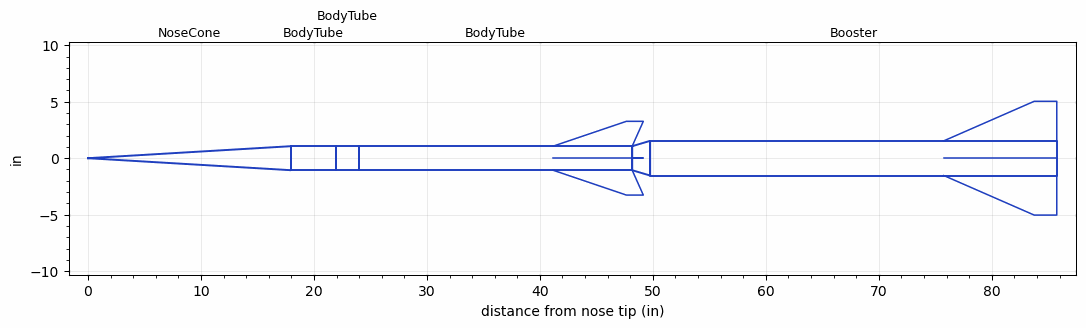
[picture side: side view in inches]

<RASAeroDocument>
 <FileVersion>2</FileVersion>
 <RocketDesign>
  <NoseCone>
   <Length>17.9685</Length>
   <Diameter>2.126</Diameter>
   <Shape>Conical</Shape>
   <Location>0</Location>
  </NoseCone>
  <BodyTube>
   <Length>4</Length>
   <Diameter>2.126</Diameter>
   <Location>17.9685</Location>
  </BodyTube>
  <BodyTube>
   <Length>2</Length>
   <Diameter>2.126</Diameter>
   <Location>21.9685</Location>
  </BodyTube>
  <BodyTube>
   <Length>24.2035</Length>
   <Diameter>2.126</Diameter>
   <Location>23.9685</Location>
   <Fin>
    <Count>4</Count>
    <Chord>7.0079</Chord>
    <Span>2.2008</Span>
    <SweepDistance>6.4921</SweepDistance>
    <TipChord>1.5</TipChord>
    <Thickness>0.1181</Thickness>
    <Location>7.0079</Location>
    <AirfoilSection>Subsonic NACA</AirfoilSection>
   </Fin>
  </BodyTube>
  <Booster>
   <Length>35.9999</Length>
   <Diameter>3.0709</Diameter>
   <InsideDiameter>2.126</InsideDiameter>
   <Location>48.172</Location>
   <ShoulderLength>1.5866</ShoulderLength>
   <Fin>
    <Count>4</Count>
    <Chord>10</Chord>
    <Span>3.5</Span>
    <SweepDistance>8</SweepDistance>
    <TipChord>2</TipChord>
    <Thickness>0.1181</Thickness>
    <Location>10</Location>
    <AirfoilSection>Subsonic NACA</AirfoilSection>
   </Fin>
  </Booster>
  <Surface>Rough Camouflage Paint</Surface>
  <ModifiedBarrowman>False</ModifiedBarrowman>
  <Turbulence>False</Turbulence>
  <UseBooster1>True</UseBooster1>
  <UseBooster2>False</UseBooster2>
 </RocketDesign>
 <LaunchSite>
  <Altitude>0</Altitude>
  <Pressure>29.9214</Pressure>
  <RodAngle>0</RodAngle>
  <RodLength>3.2808</RodLength>
  <Temperature>59</Temperature>
  <WindSpeed>4.4739</WindSpeed>
 </LaunchSite>
 <Recovery>
  <Altitude1>656.168</Altitude1>
  <Altitude2>0</Altitude2>
  <DeviceType1>Parachute</DeviceType1>
  <DeviceType2>None</DeviceType2>
  <Event1>True</Event1>
  <Event2>False</Event2>
  <Size1>47.9999</Size1>
  <Size2>0</Size2>
  <EventType1>Apogee</EventType1>
  <EventType2>None</EventType2>
  <CD1>0.8</CD1>
  <CD2>0</CD2>
 </Recovery>
 <SimulationList>
  <Simulation>
   <SustainerEngine>K1100T  (AT)</SustainerEngine>
   <SustainerLaunchWt>6.3637</SustainerLaunchWt>
   <SustainerCG>32.1403</SustainerCG>
   <SustainerIgnitionDelay>0</SustainerIgnitionDelay>
   <Booster1Engine>L1040DM-P  (AT)</Booster1Engine>
   <Booster1LaunchWt>22.1917</Booster1LaunchWt>
   <Booster1SeparationDelay>0</Booster1SeparationDelay>
   <Booster1IgnitionDelay>0</Booster1IgnitionDelay>
   <Booster1CG>58.7903</Booster1CG>
   <IncludeBooster1>True</IncludeBooster1>
   <Booster2Delay>0</Booster2Delay>
   <IncludeBooster2>False</IncludeBooster2>
   <TimetoApogee>36.30061</TimetoApogee>
   <MaxAltitude>27900.15</MaxAltitude>
   <MaxVelocity>2681.434</MaxVelocity>
   <OptimumWt>7.795533</OptimumWt>
   <OptimumMaxAlt>7.795533</OptimumMaxAlt>
  </Simulation>
  <Simulation>
   <SustainerEngine>K250W  (AT)</SustainerEngine>
   <SustainerLaunchWt>8.3173</SustainerLaunchWt>
   <SustainerCG>30.8926</SustainerCG>
   <SustainerIgnitionDelay>7</SustainerIgnitionDelay>
   <Booster1Engine>L1040DM-P  (AT)</Booster1Engine>
   <Booster1LaunchWt>24.1453</Booster1LaunchWt>
   <Booster1SeparationDelay>0</Booster1SeparationDelay>
   <Booster1IgnitionDelay>0</Booster1IgnitionDelay>
   <Booster1CG>56.2042</Booster1CG>
   <IncludeBooster1>True</IncludeBooster1>
   <Booster2Delay>0</Booster2Delay>
   <IncludeBooster2>False</IncludeBooster2>
   <TimetoApogee>54.99747</TimetoApogee>
   <MaxAltitude>47185.95</MaxAltitude>
   <MaxVelocity>2121.661</MaxVelocity>
   <OptimumWt>6.757806</OptimumWt>
   <OptimumMaxAlt>6.757806</OptimumMaxAlt>
  </Simulation>
 </SimulationList>
</RASAeroDocument>
